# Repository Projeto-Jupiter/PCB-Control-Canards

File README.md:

# PCB-Control-Canards
PCB for the active control of roll speed of Juninho, Nyx and Ganímedes

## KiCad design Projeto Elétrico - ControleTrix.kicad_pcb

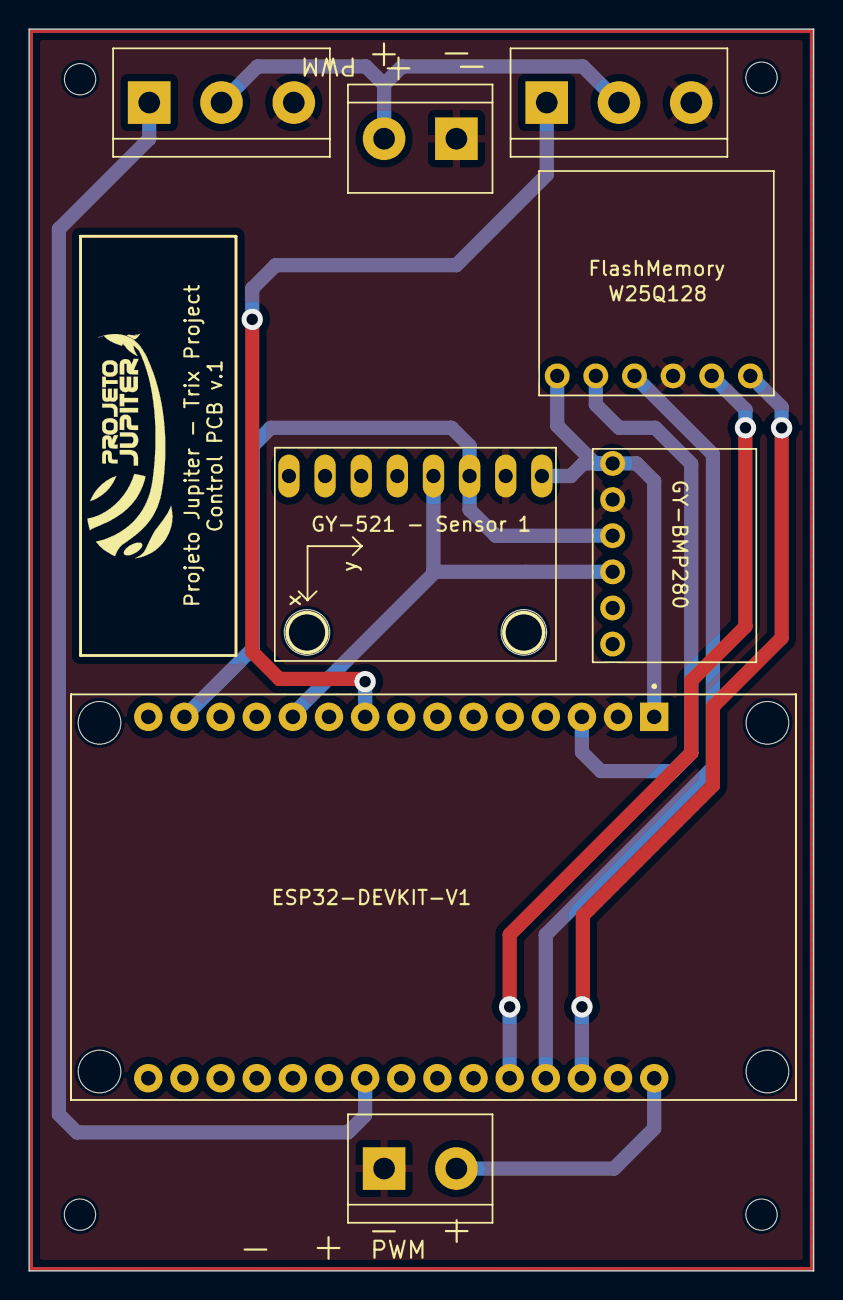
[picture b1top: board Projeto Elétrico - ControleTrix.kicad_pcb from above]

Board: 2 copper layers, 55.1 x 87.3 mm, 8 parts (0 on the bottom side), 11 nets.

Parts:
J1, J1#2: Power Supply; TerminalBlock_bornier-2_P5.08mm
J2, J3: Conn_01x03_Male; TerminalBlock_bornier-3_P5.08mm
U1: ESP32-DEVKIT-V1; MODULE_ESP32_DEVKIT_V1
U3: FlashMemory; FlashMemory W25Q128
U4: GY-521 - Sensor 1; GY-521
U6: GY-BMP280; GY BMP280

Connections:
/3v3: U1.1 (3V3), U3.1 (Vcc), U4.VCC, U6.1 (VCC)
/CS: U1.3 (D15), U3.2 (CS)
/HCLK: U1.26 (D14), U3.5 (CLK)
/HMISO: U1.27 (D12), U3.3 (DO)
/HMOSI: U1.28 (D13), U3.6 (DI)
/PWM 1: J2.1, U1.22 (D33)
/PWM 2: J3.1, U1.9 (D18)
/SCL: U1.14 (D22), U4.SCL, U6.3 (SCL)
/SDA: U1.11 (D21), U4.SDA, U6.4 (SDA)
GND: J1.1, J1#2.1, J2.3, J3.3, U1.2 (GND), U1.29 (GND), U3.4 (GND), U4.GND, U6.2 (GND)
VCC: J1.2, J1#2.2, J2.2, J3.2, U1.30 (VIN)

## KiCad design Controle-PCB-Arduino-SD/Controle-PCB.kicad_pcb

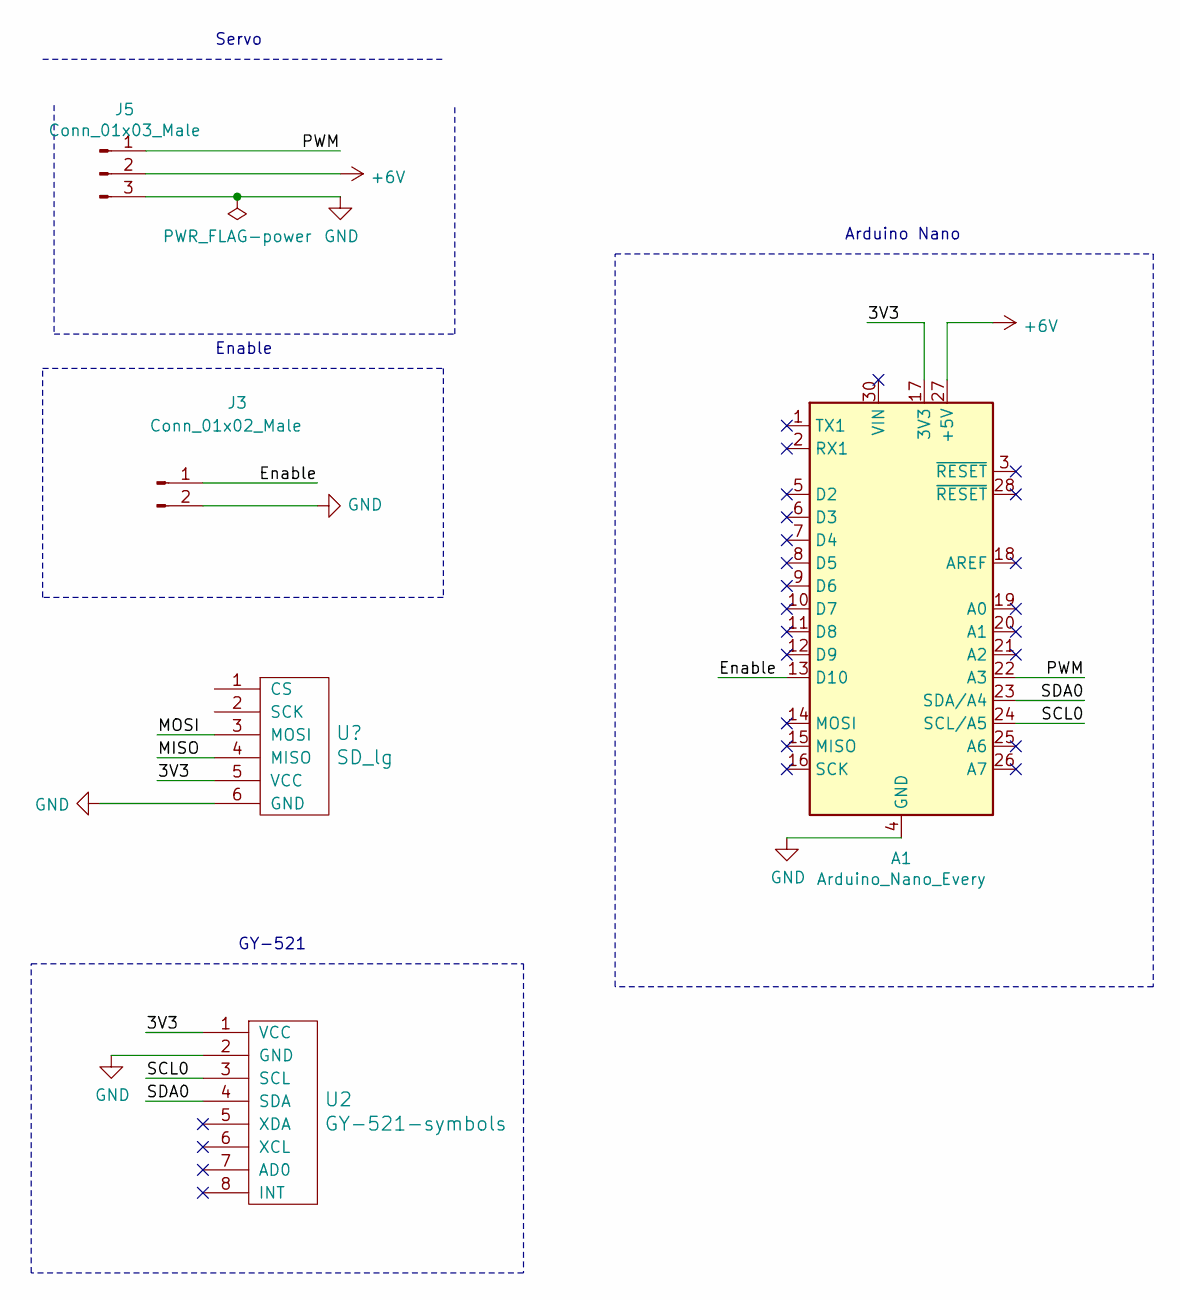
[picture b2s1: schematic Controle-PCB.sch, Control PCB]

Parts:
A1: Arduino_Nano_Every; Arduino_Nano
J3: Conn_01x02_Male; PinHeader_1x02_P2.54mm_Vertical
J5: Conn_01x03_Male; PinHeader_1x03_P2.54mm_Vertical
U2: GY-521-symbols; GY-521

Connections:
+6V: A1.27 (+5V), J5.2
/3V3: A1.17 (3V3), U2.1 (VCC)
/Enable: A1.13 (D10), J3.1
/PWM: A1.22 (A3), J5.1
/SCL0: A1.24 (SCL/A5), U2.3 (SCL)
/SDA0: A1.23 (SDA/A4), U2.4 (SDA)
GND: A1.4 (GND), A1.29 (GND), J3.2, J5.3, U2.2 (GND)

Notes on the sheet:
Enable
Servo
Arduino Nano
GY-521

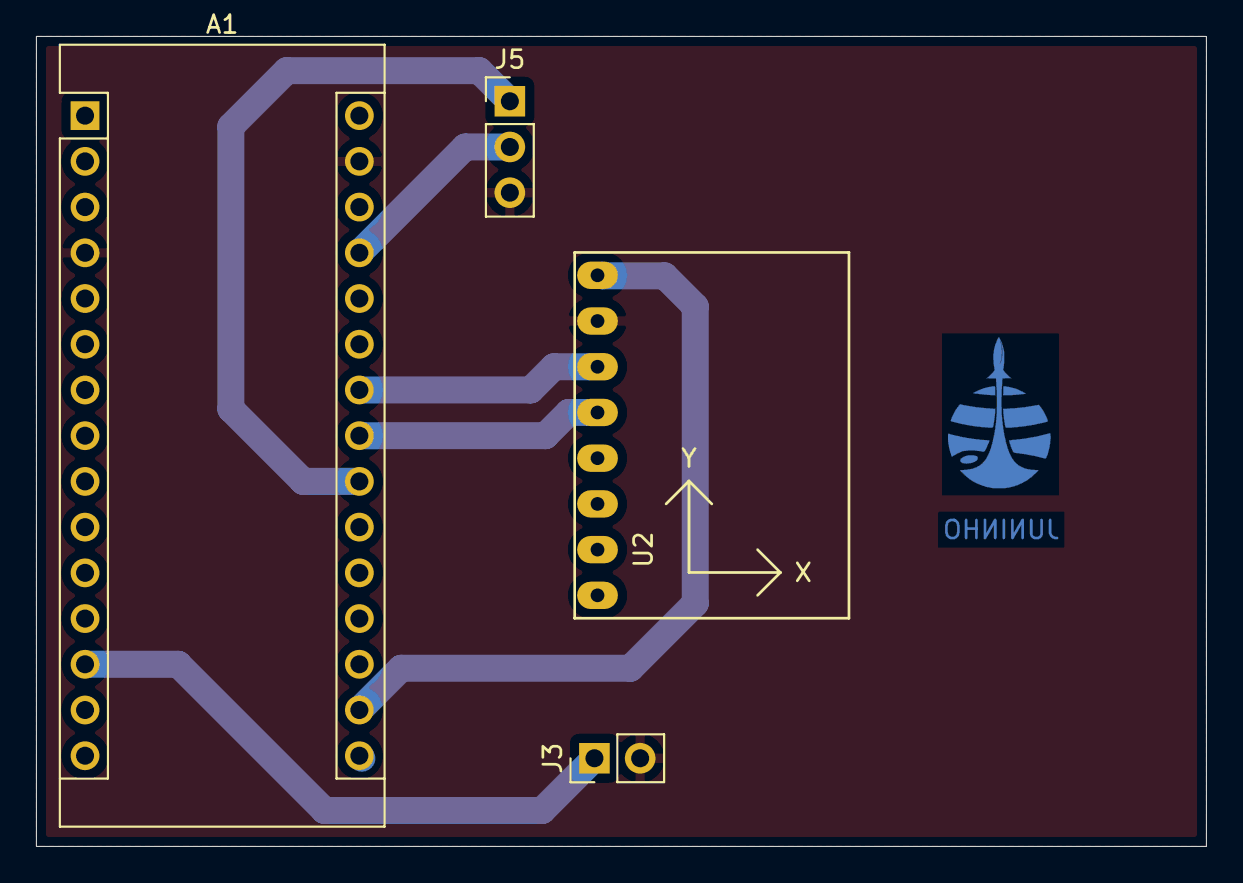
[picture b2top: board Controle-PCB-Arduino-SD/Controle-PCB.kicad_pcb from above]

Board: 2 copper layers, 65.0 x 45.0 mm, 4 parts (0 on the bottom side), 7 nets.

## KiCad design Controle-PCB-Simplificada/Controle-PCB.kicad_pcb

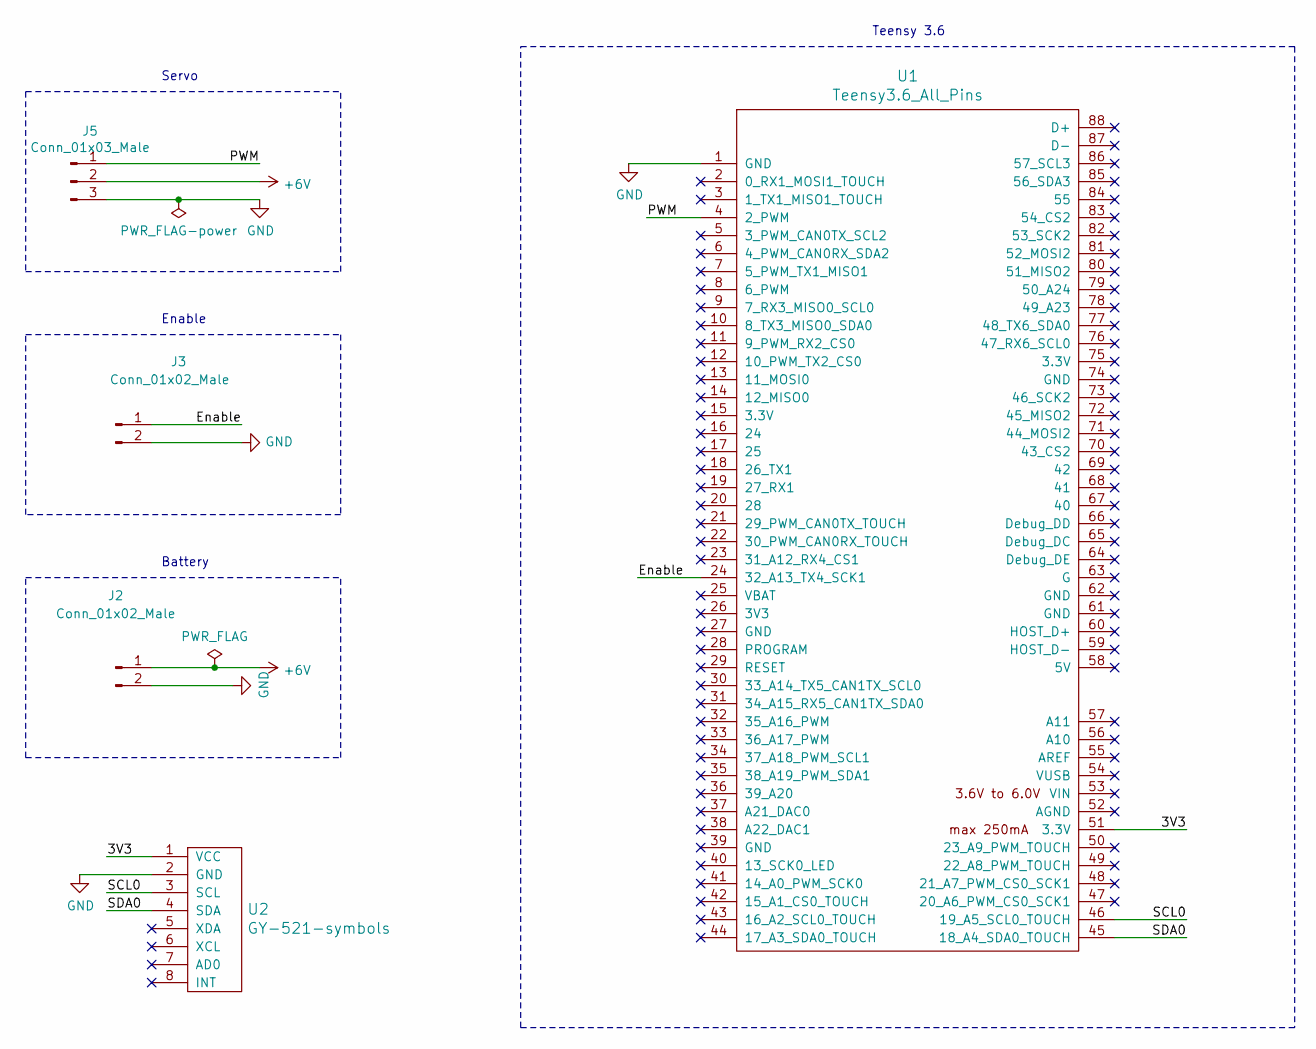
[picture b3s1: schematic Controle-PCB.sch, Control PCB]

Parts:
J2: Conn_01x02_Male; JS-1001-02
J3: Conn_01x02_Male; PinHeader_1x02_P2.54mm_Vertical
J5: Conn_01x03_Male; PinHeader_1x03_P2.54mm_Vertical
U1: Teensy3.6_All_Pins; Teensy35_36_All_Pins
U2: GY-521-symbols; GY-521

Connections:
+6V: J2.1, J5.2
/3V3: U1.51 (3.3V), U2.1 (VCC)
/Enable: J3.1, U1.24 (32_A13_TX4_SCK1)
/PWM: J5.1, U1.4 (2_PWM)
/SCL0: U1.46 (19_A5_SCL0_TOUCH), U2.3 (SCL)
/SDA0: U1.45 (18_A4_SDA0_TOUCH), U2.4 (SDA)
GND: J2.2, J3.2, J5.3, U1.1 (GND), U2.2 (GND)

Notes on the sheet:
Teensy 3.6
Enable
Battery
Servo

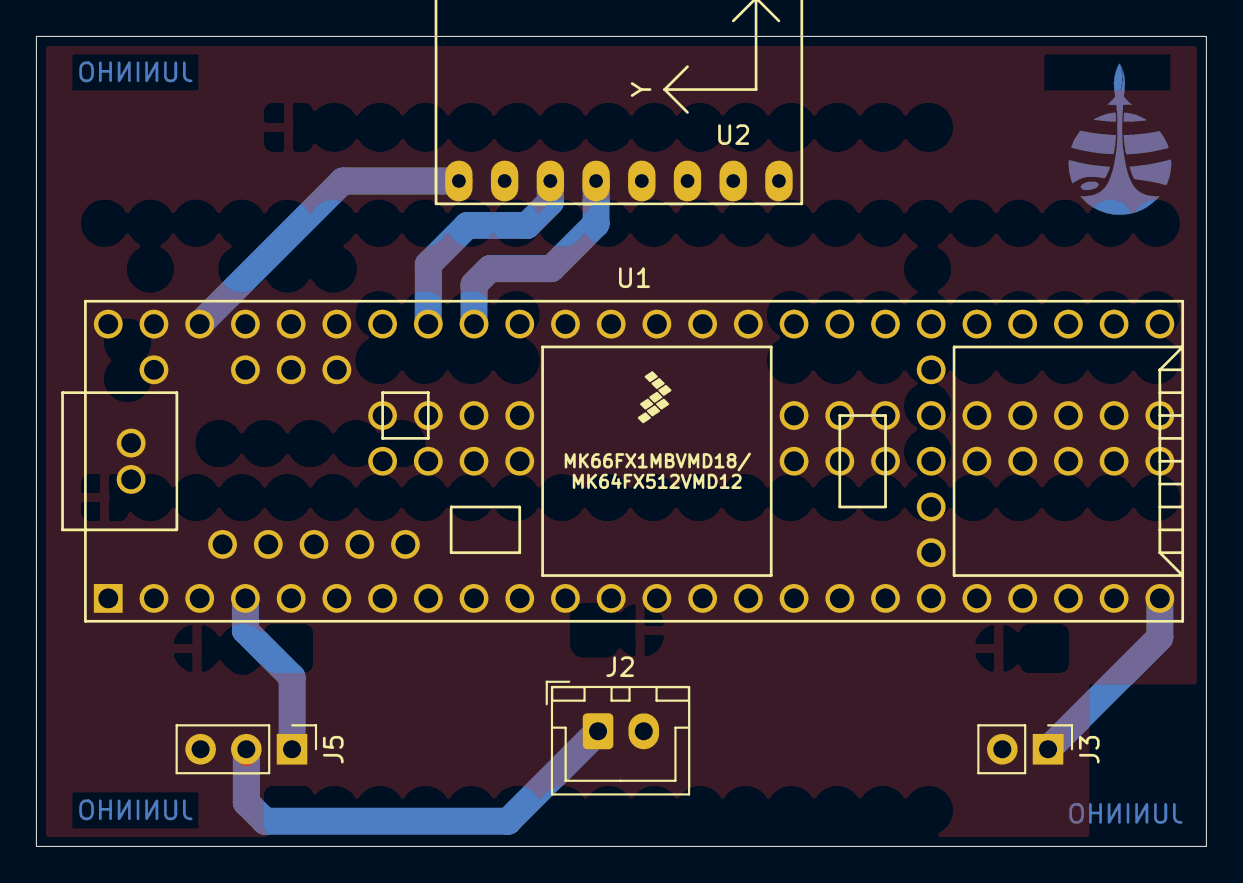
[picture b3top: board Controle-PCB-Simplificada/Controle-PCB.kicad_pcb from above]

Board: 2 copper layers, 65.0 x 45.0 mm, 5 parts (0 on the bottom side), 7 nets.

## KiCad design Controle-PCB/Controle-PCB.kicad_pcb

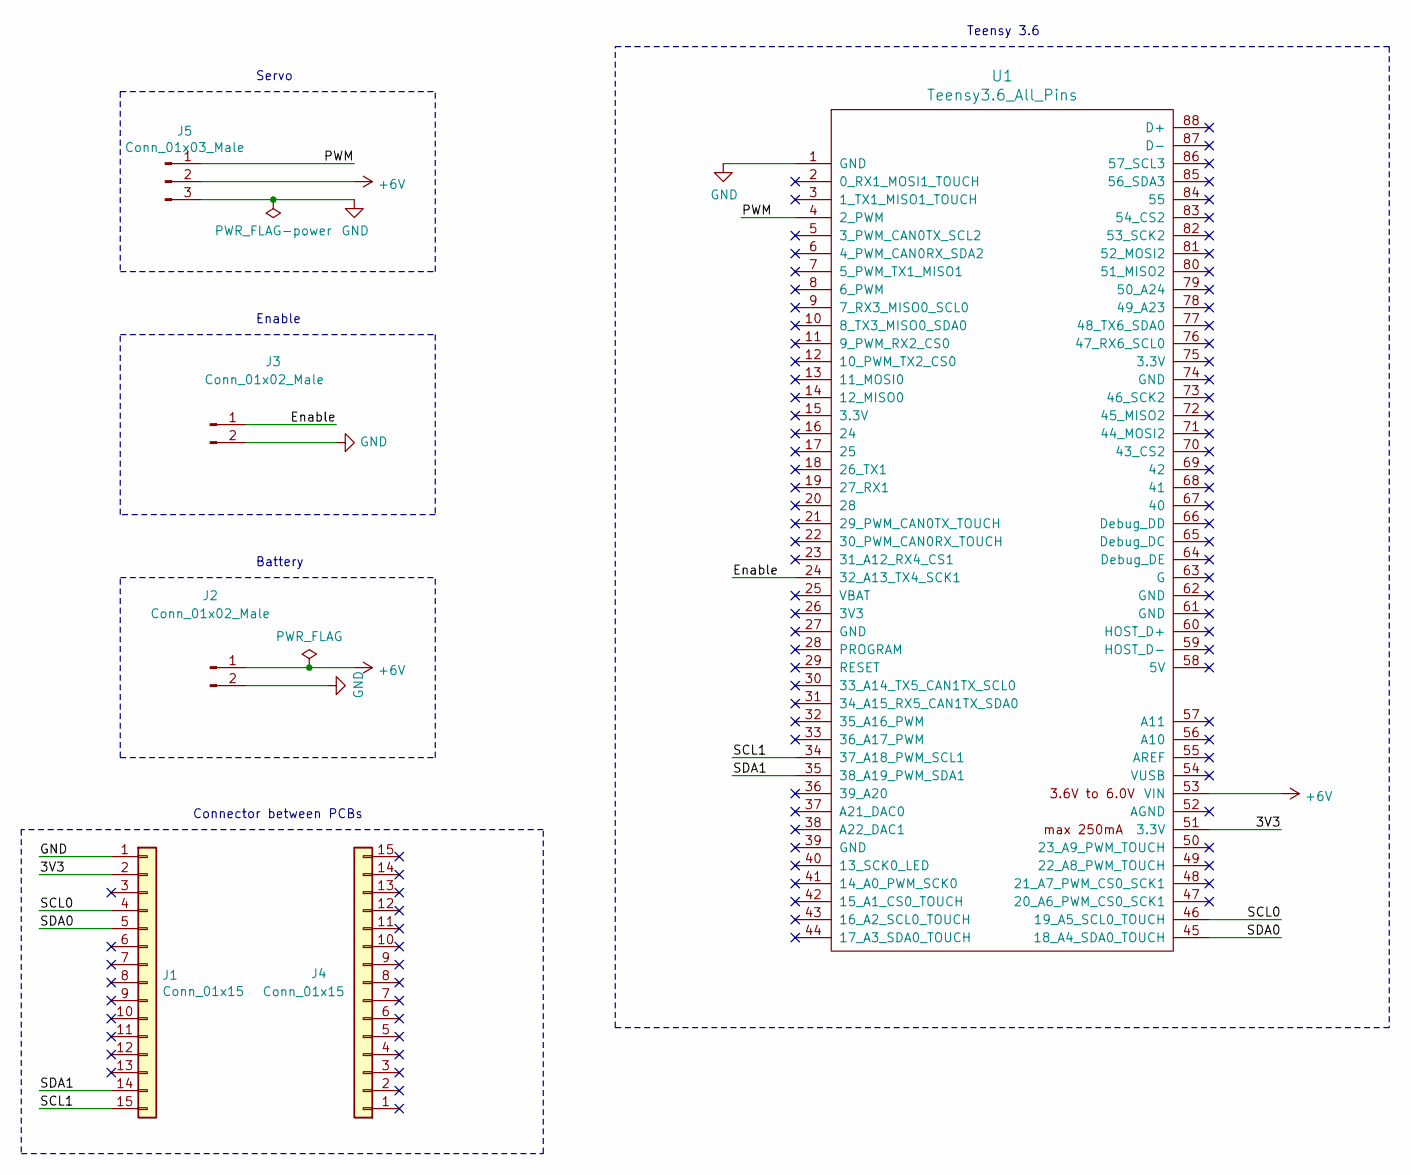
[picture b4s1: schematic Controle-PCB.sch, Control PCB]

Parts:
J1, J4: Conn_01x15; PinHeader_1x15_P2.54mm_Vertical
J2: Conn_01x02_Male; JS-1001-02
J3: Conn_01x02_Male; PinHeader_1x02_P2.54mm_Vertical
J5: Conn_01x03_Male; PinHeader_1x03_P2.54mm_Vertical
U1: Teensy3.6_All_Pins; Teensy35_36_All_Pins

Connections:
+6V: J2.1, J5.2, U1.53 (VIN)
/3V3: J1.2, U1.51 (3.3V)
/Enable: J3.1, U1.24 (32_A13_TX4_SCK1)
/PWM: J5.1, U1.4 (2_PWM)
/SCL0: J1.4, U1.46 (19_A5_SCL0_TOUCH)
/SCL1: J1.15, U1.34 (37_A18_PWM_SCL1)
/SDA0: J1.5, U1.45 (18_A4_SDA0_TOUCH)
/SDA1: J1.14, U1.35 (38_A19_PWM_SDA1)
GND: J1.1, J2.2, J3.2, J5.3, U1.1 (GND)

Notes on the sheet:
Teensy 3.6
Enable
Battery
Connector between PCBs
Servo

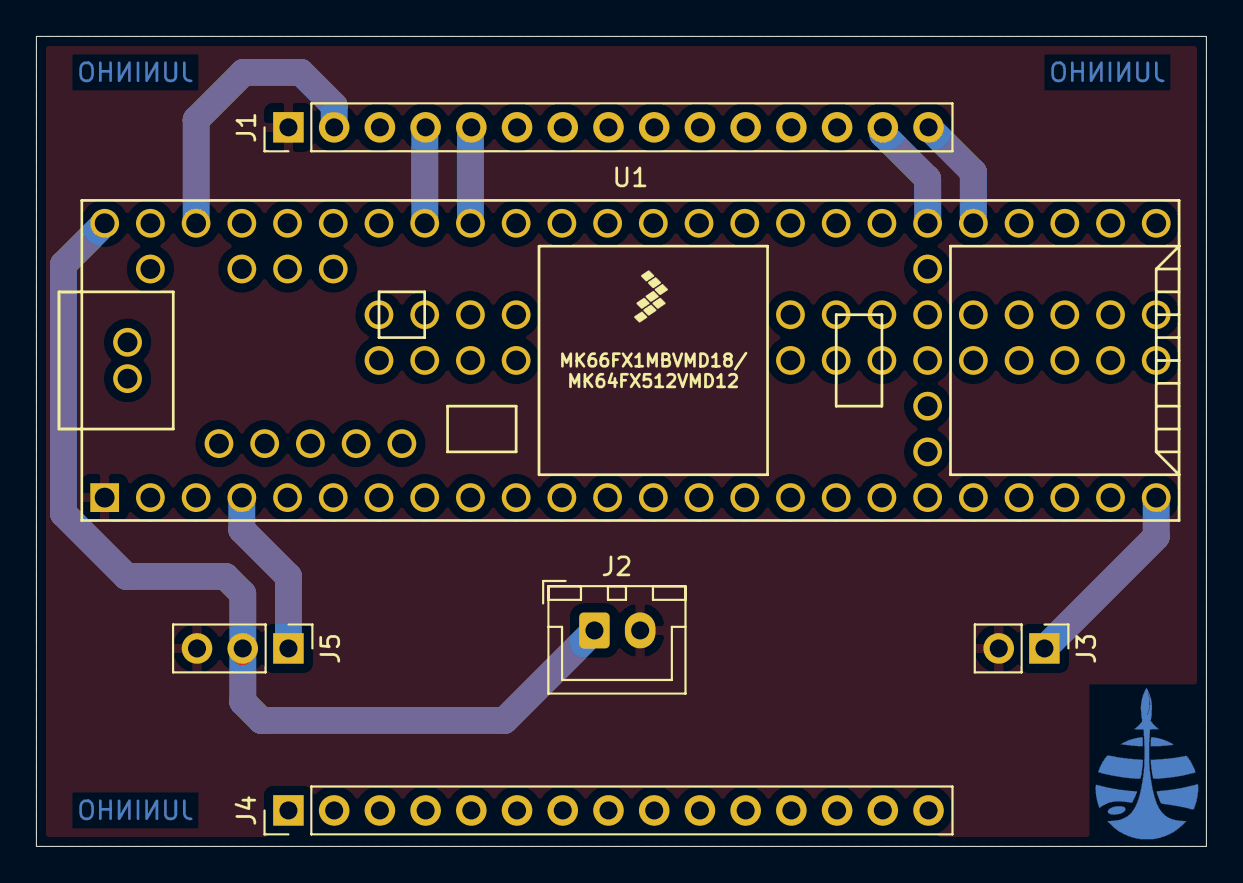
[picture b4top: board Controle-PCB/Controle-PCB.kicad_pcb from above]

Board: 2 copper layers, 65.0 x 45.0 mm, 6 parts (0 on the bottom side), 9 nets.

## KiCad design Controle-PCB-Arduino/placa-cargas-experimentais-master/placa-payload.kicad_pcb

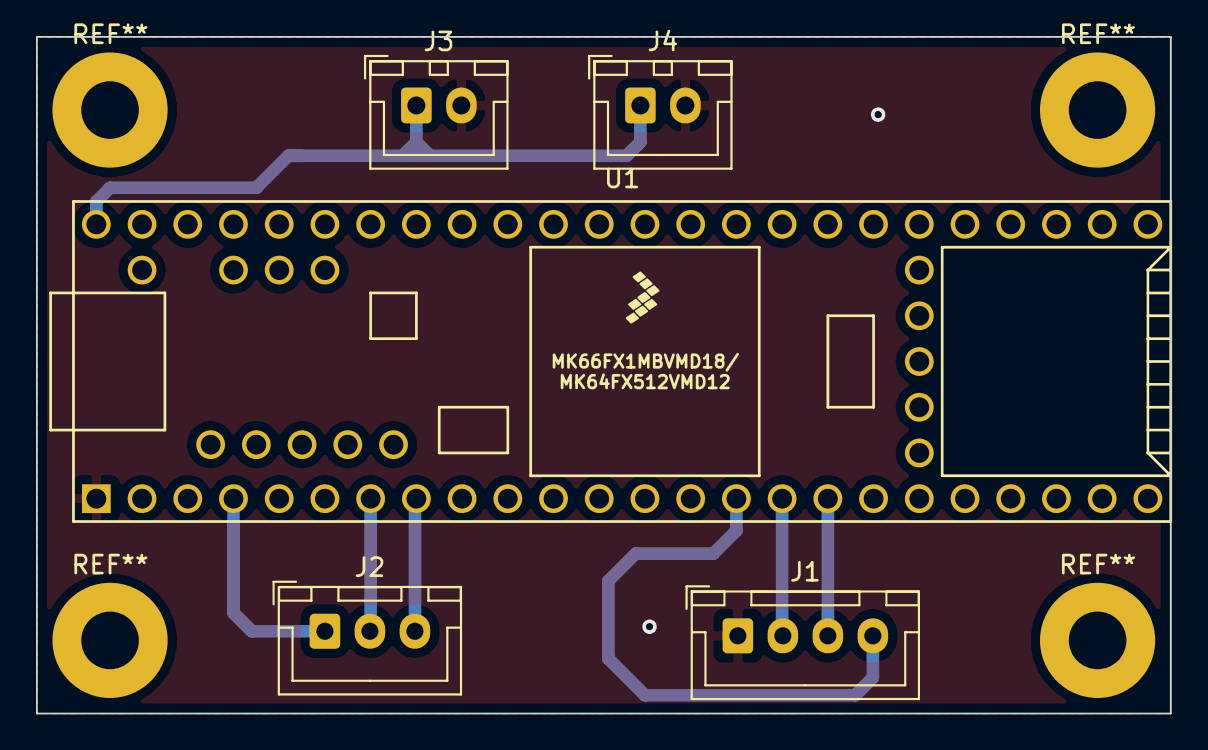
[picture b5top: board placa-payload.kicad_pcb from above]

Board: 2 copper layers, 63.0 x 37.6 mm, 5 parts (0 on the bottom side), 8 nets.

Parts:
J1: Encoder; JST_XH_B4B-XH-A_1x04_P2.50mm_Vertical
J2: Driver_control; JST_XH_B3B-XH-A_1x03_P2.50mm_Vertical
J3: Driver_power; JST_XH_B2B-XH-A_1x02_P2.50mm_Vertical
J4: Battery; JST_XH_B2B-XH-A_1x02_P2.50mm_Vertical
U1: Teensy3.6; Teensy35_36

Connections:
+3V3: J1.4, U1.15
+6V: J3.1, J4.1, U1.53
/Driver_PWM: J2.1, U1.4
/Encoder_A: J1.2, U1.16
/Encoder_B: J1.3, U1.17
/Motor_rotation_0: J2.2, U1.7
/Motor_rotation_1: J2.3, U1.8
GND: J1.1, J3.2, J4.2, U1.1

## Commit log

2022-01-14 Add Board 1 PCB print files
2022-01-14 Create oi
2022-01-14 Added first PCB
2022-01-14 Added second PCB
2022-01-14 Fixed directories
2022-01-17 PCB changes
2022-02-17 Final version
2022-04-07 Added simplified version of PCB
2022-04-09 pcbs
2022-06-10 last Changes (april 9th 2022)
2022-10-30 First version of Control PCB - Nyx Project
2022-10-31 Symbols and Footprints upload
2022-11-03 -m uploads on PCB and Schematic projects
2022-11-07 Pull-up Resistors added.
2022-11-23 First final version
2023-01-02 PCB files - final version
2023-05-26 Create Test
2023-05-26 Create Controle-PCB-GanímedesProject
2023-05-26 Create Teste
2023-05-26 Create A
2023-06-05 PCB Ganimedes embelezada
2023-11-19 PCB roll trix
2023-11-20 Add files via upload
    Atualização da posição dos bornes
2023-11-20 Add files via upload
    Airbrake Software Test
